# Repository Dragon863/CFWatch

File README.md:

# ⌚ CFWatch

## What is this?

CFWatch is a project that I've been wanting to build for years now. I've always dreamed of building a watch, but was never quite sure where to start - sure, the pinetime and other hackable watches were really cool, but they never quite felt "personal" or quite reflective of the stuff I enjoy. Eventually I decided I'd just build my own, but I didn't really have the knowledge or skills to do so until very recently, so when [highway](https://highway.hackclub.com/) came along I decided it was finally time! The "CF" in "CFWatch" came from [r/cassettefuturism](https://old.reddit.com/r/cassettefuturism/top/?sort=top&t=all), a huge source of design inspiration for this

## Hardware Overview (Bill of Material)

| Description | Count |
| -------- | ------- |
| USB-C charging & programming (requires bootloader) | 1 |
| red 7-segment displays | 4 |
| individually programmable buttons | 2 |
| LIR2032 battery with theoretical battery life of several months (untested) | 1 |
| SAMD21 microcontroller for low power usage | 1 |

The board layout is optimised for being assembled with JLCPCB's PCBA service, with every component apart from the battery on the front of the PCB. I would recommend hand soldering the cell mount to save costs.

## Repository Layout

The repo is structured as follows:
- PCB-related KiCad files in the `PCB/`
- FreeCAD case design in `CAD/`
- Files for creating the cover render in `Blender/`
- For a rough BOM, see `BOM.csv`
- For my development log, see `JOURNAL.md

> [!CAUTION]
> Version 1 has SEVERAL known issues! If you plan to use this to have your own manufactured, please use the V2 design made in EasyEDA and double check everything in the schematic and PCB; I am not responsible for any non-functional boards!

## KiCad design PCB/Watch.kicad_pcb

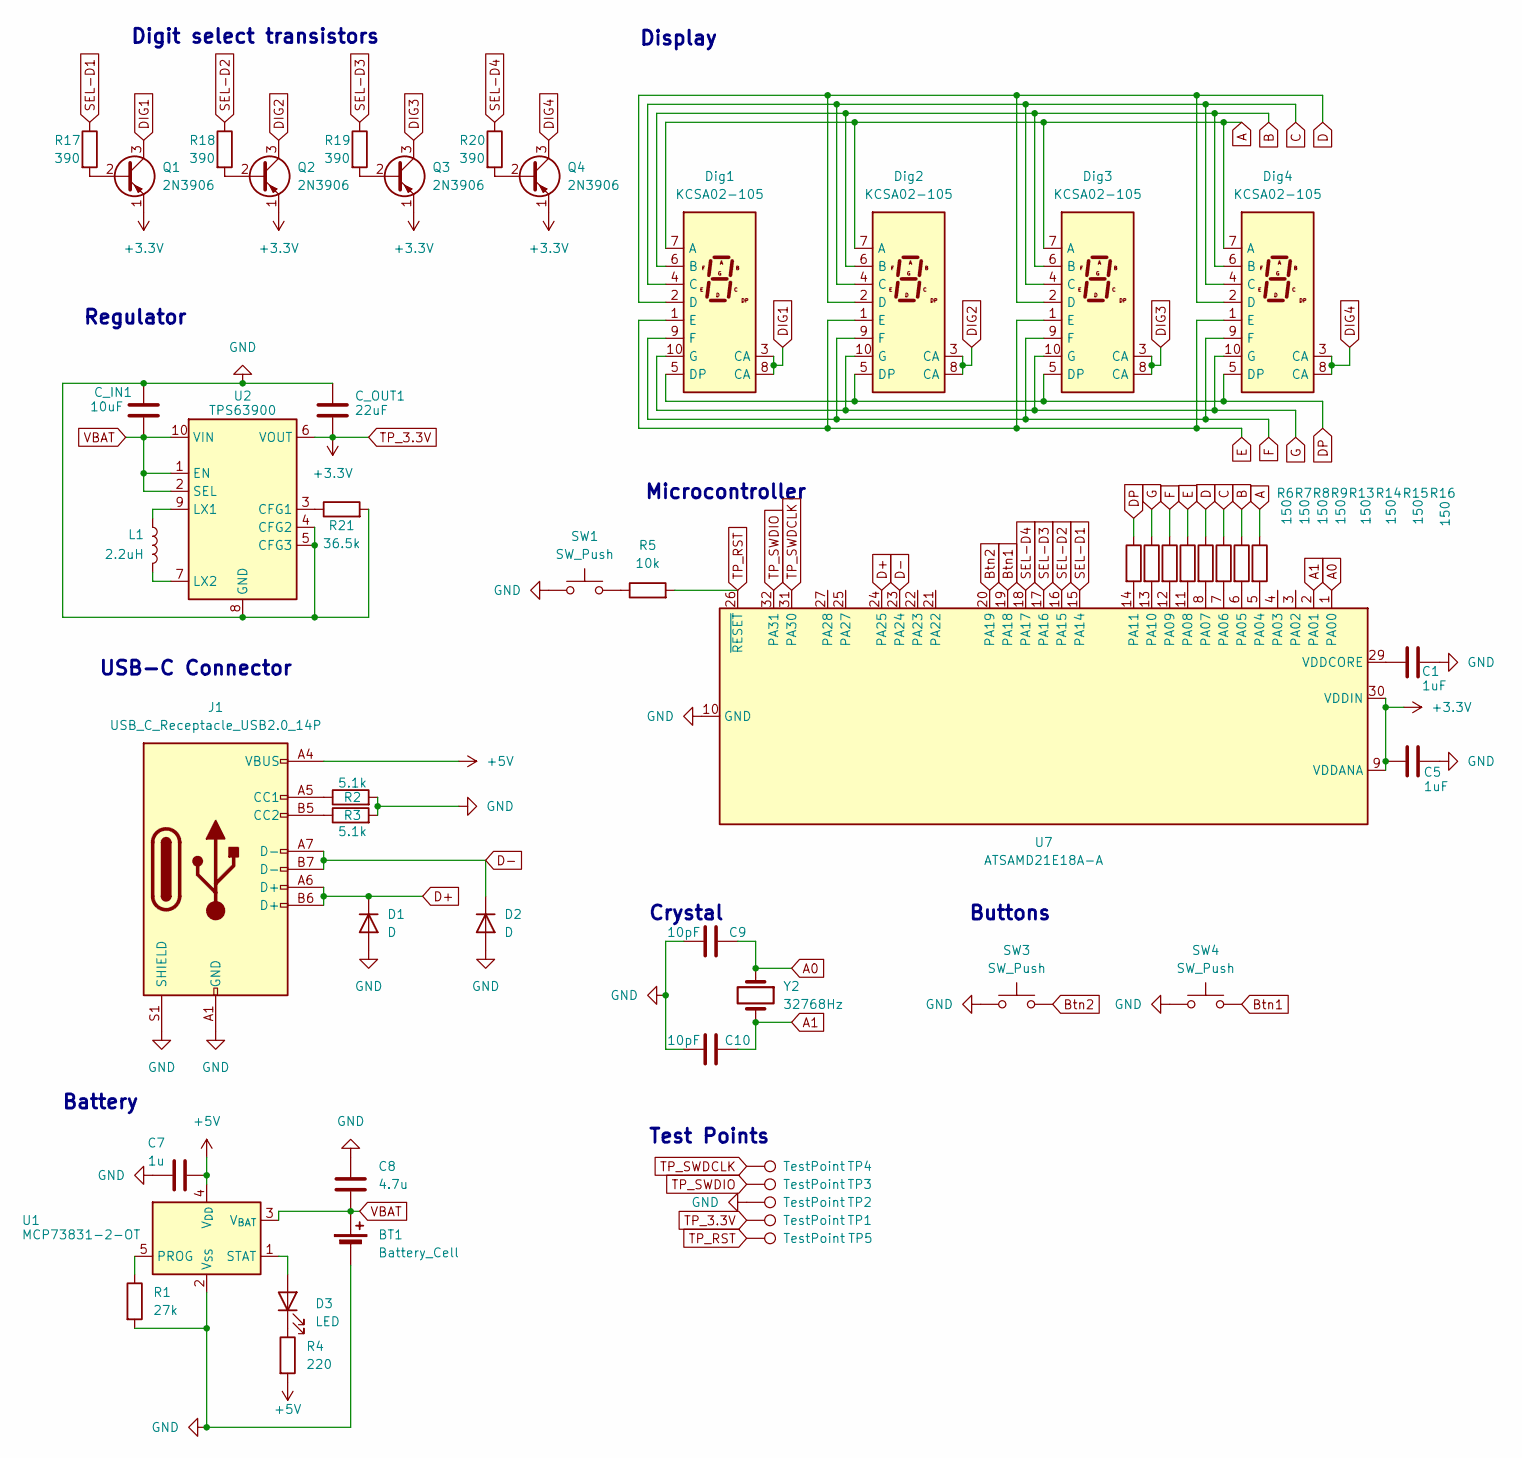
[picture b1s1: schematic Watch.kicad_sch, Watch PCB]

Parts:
BT1: Battery_Cell; BatteryHolder_Keystone_1060_1x2032
C1, C5: 1uF; C_0402_1005Metric
C7: 1u; C_0402_1005Metric
C8: 4.7u; C_0603_1608Metric
C9, C10: 10pF; C_0402_1005Metric; MPN CL21C100JBANNNC
C_IN1: 10uF; C_0603_1608Metric
C_OUT1: 22uF; C_0603_1608Metric
D1, D2: D; D_SOD-323
D3: LED; LED_0402_1005Metric
Dig1, Dig2, Dig3, Dig4: KCSA02-105; KCSC02-105
J1: USB_C_Receptacle_USB2.0_14P; USB_C_Receptacle_HCTL_HC-TYPE-C-16P-01A
L1: 2.2uH; L_0805_2012Metric
Q1, Q2, Q3, Q4: 2N3906; SOT-23
R1: 27k; R_0402_1005Metric
R2, R3: 5.1k; R_0402_1005Metric
R4: 220; R_0402_1005Metric
R5: 10k; R_0402_1005Metric
R6, R7, R8, R9, R13, R14, R15, R16: 150; R_0402_1005Metric
R17, R18, R19, R20: 390; R_0402_1005Metric
R21: 36.5k; R_0402_1005Metric
SW1, SW3, SW4: SW_Push; SW_SPST_B3U-1000P
TP1, TP2, TP3, TP4, TP5: TestPoint; TestPoint_Pad_D1.0mm
U1: MCP73831-2-OT; SOT-23-5
U2: TPS63900; WSON-10-1EP_2.5x2.5mm_P0.5mm_EP1.2x2mm_ThermalVias
U7: ATSAMD21E18A-A; TQFP-32_7x7mm_P0.8mm
Y2: 32768Hz; Crystal_SMD_3215-2Pin_3.2x1.5mm

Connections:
+5V: C7.2, J1.A4 (VBUS), J1.A9 (VBUS), J1.B4 (VBUS), J1.B9 (VBUS), R4.2, U1.4 (V_{DD})
A: Dig1.7 (A), Dig2.7 (A), Dig3.7 (A), Dig4.7 (A), R16.1
A0: C9.1, U7.1 (PA00), Y2.1
A1: C10.1, U7.2 (PA01), Y2.2
B: Dig1.6 (B), Dig2.6 (B), Dig3.6 (B), Dig4.6 (B), R15.1
Btn1: SW4.2, U7.19 (PA18)
Btn2: SW3.2, U7.20 (PA19)
C: Dig1.4 (C), Dig2.4 (C), Dig3.4 (C), Dig4.4 (C), R14.1
D: Dig1.2 (D), Dig2.2 (D), Dig3.2 (D), Dig4.2 (D), R13.1
D+: D1.1 (K), J1.A6 (D+), J1.B6 (D+), U7.24 (PA25)
D-: D2.1 (K), J1.A7 (D-), J1.B7 (D-), U7.23 (PA24)
DIG1: Dig1.3 (CA), Dig1.8 (CA), Q1.3 (C)
DIG2: Dig2.3 (CA), Dig2.8 (CA), Q2.3 (C)
DIG3: Dig3.3 (CA), Dig3.8 (CA), Q3.3 (C)
DIG4: Dig4.3 (CA), Dig4.8 (CA), Q4.3 (C)
DP: Dig1.5 (DP), Dig2.5 (DP), Dig3.5 (DP), Dig4.5 (DP), R6.1
E: Dig1.1 (E), Dig2.1 (E), Dig3.1 (E), Dig4.1 (E), R9.1
F: Dig1.9 (F), Dig2.9 (F), Dig3.9 (F), Dig4.9 (F), R8.1
G: Dig1.10 (G), Dig2.10 (G), Dig3.10 (G), Dig4.10 (G), R7.1
unnamed: D3.2 (A), U1.1 (STAT)
unnamed: D3.1 (K), R4.1
unnamed: J1.A5 (CC1), R2.1
unnamed: J1.B5 (CC2), R3.1
unnamed: Q1.2 (B), R17.2
unnamed: Q2.2 (B), R18.2
unnamed: Q3.2 (B), R19.2
unnamed: Q4.2 (B), R20.2
unnamed: R5.1, SW1.2
unnamed: R1.1, U1.5 (PROG)
unnamed: R21.1, U2.3 (CFG1)
unnamed: L1.1, U2.9 (LX1)
unnamed: L1.2, U2.7 (LX2)
unnamed: R16.2, U7.5 (PA04)
unnamed: R15.2, U7.6 (PA05)
unnamed: R14.2, U7.7 (PA06)
unnamed: R13.2, U7.8 (PA07)
unnamed: R9.2, U7.11 (PA08)
unnamed: R8.2, U7.12 (PA09)
unnamed: R7.2, U7.13 (PA10)
unnamed: R6.2, U7.14 (PA11)
unnamed: C1.1, U7.29 (VDDCORE)
SEL-D1: R17.1, U7.15 (PA14)
SEL-D2: R18.1, U7.16 (PA15)
SEL-D3: R19.1, U7.17 (PA16)
SEL-D4: R20.1, U7.18 (PA17)
TP_3.3V: C5.1, C_OUT1.2, Q1.1 (E), Q2.1 (E), Q3.1 (E), Q4.1 (E), TP1.1, U2.6 (VOUT), U7.9 (VDDANA), U7.30 (VDDIN)
TP_RST: R5.2, TP5.1, U7.26 (~RESET)
TP_SWDCLK: TP4.1, U7.31 (PA30)
TP_SWDIO: TP3.1, U7.32 (PA31)

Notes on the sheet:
Battery
Crystal
Display
Test Points
Microcontroller
Digit select transistors
Regulator
Buttons
USB-C Connector

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
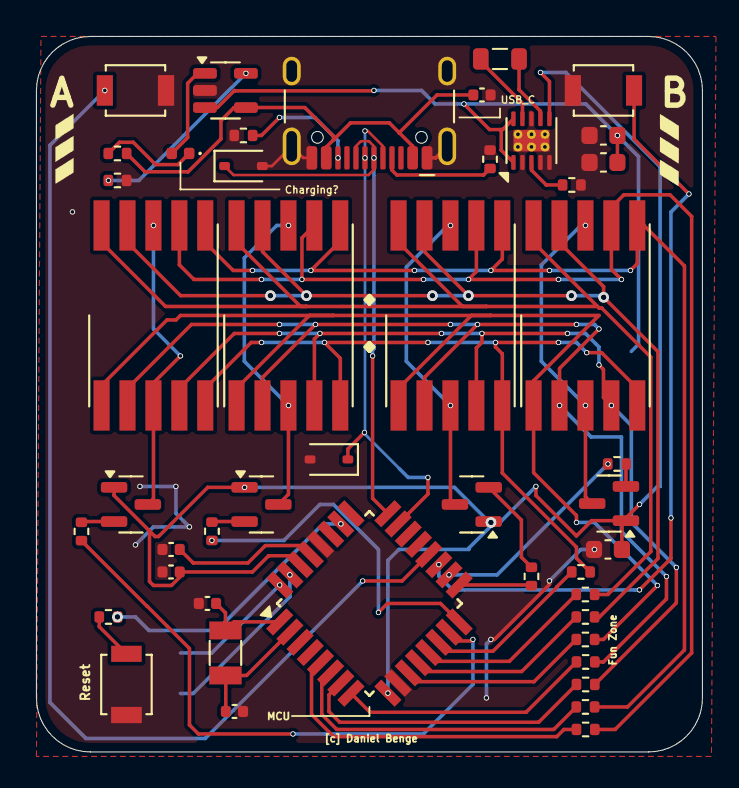
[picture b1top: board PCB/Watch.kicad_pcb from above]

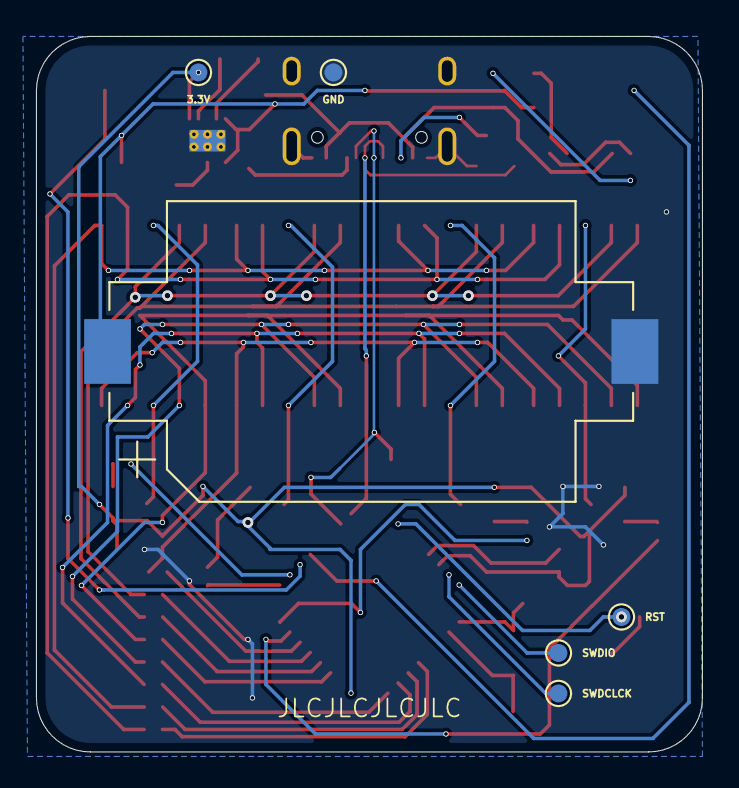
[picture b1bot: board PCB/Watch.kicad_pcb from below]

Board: 2 copper layers, 37.0 x 39.8 mm, 54 parts (6 on the bottom side), 51 nets.

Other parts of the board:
G1: LOGO
graphic2: LOGO

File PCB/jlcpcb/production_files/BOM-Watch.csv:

Comment,Designator,Footprint,LCSC,Quantity
2.2uH,L1,L_0805_2012Metric,C1043,1
MCP73831-2-OT,U1,SOT-23-5,C14879,1
36.5k,R21,R_0402_1005Metric,C15011,1
TPS63900,U2,WSON-10-1EP_2.5x2.5mm_P0.5mm_EP1.2x2mm_ThermalVias,C1518762,1
D,"D1,D2",D_SOD-323,C191023,2
4.7u,C8,C_0603_1608Metric,C19666,1
KCSA02-105,"Dig1,Dig2,Dig3,Dig4",KCSC02-105,C22462656,4
SW_Push,"SW1,SW3,SW4",SW_SPST_B3U-1000P,C231329,3
150,"R13,R14,R15,R16,R6,R7,R8,R9",R_0402_1005Metric,C25082,8
220,R4,R_0402_1005Metric,C25091,1
390,"R17,R18,R19,R20",R_0402_1005Metric,C25109,4
10k,R5,R_0402_1005Metric,C25744,1
27k,R1,R_0402_1005Metric,C25771,1
5.1k,"R2,R3",R_0402_1005Metric,C25905,2
USB_C_Receptacle_USB2.0_14P,J1,USB_C_Receptacle_HCTL_HC-TYPE-C-16P-01A,C2988369,1
32768Hz,Y2,Crystal_SMD_3215-2Pin_3.2x1.5mm,C32346,1
10pF,"C10,C9",C_0402_1005Metric,C32949,2
LED,D3,LED_0402_1005Metric,C33115,1
1uF,"C1,C5,C6,C7",C_0402_1005Metric,C52923,4
2N3906,"Q1,Q2,Q3,Q4",SOT-23,C5300004,4
22uF,C_OUT1,C_0603_1608Metric,C59461,1
ATSAMD21E18A-A,U7,TQFP-32_7x7mm_P0.8mm,C618770,1
10uF,C_IN1,C_0603_1608Metric,C96446,1

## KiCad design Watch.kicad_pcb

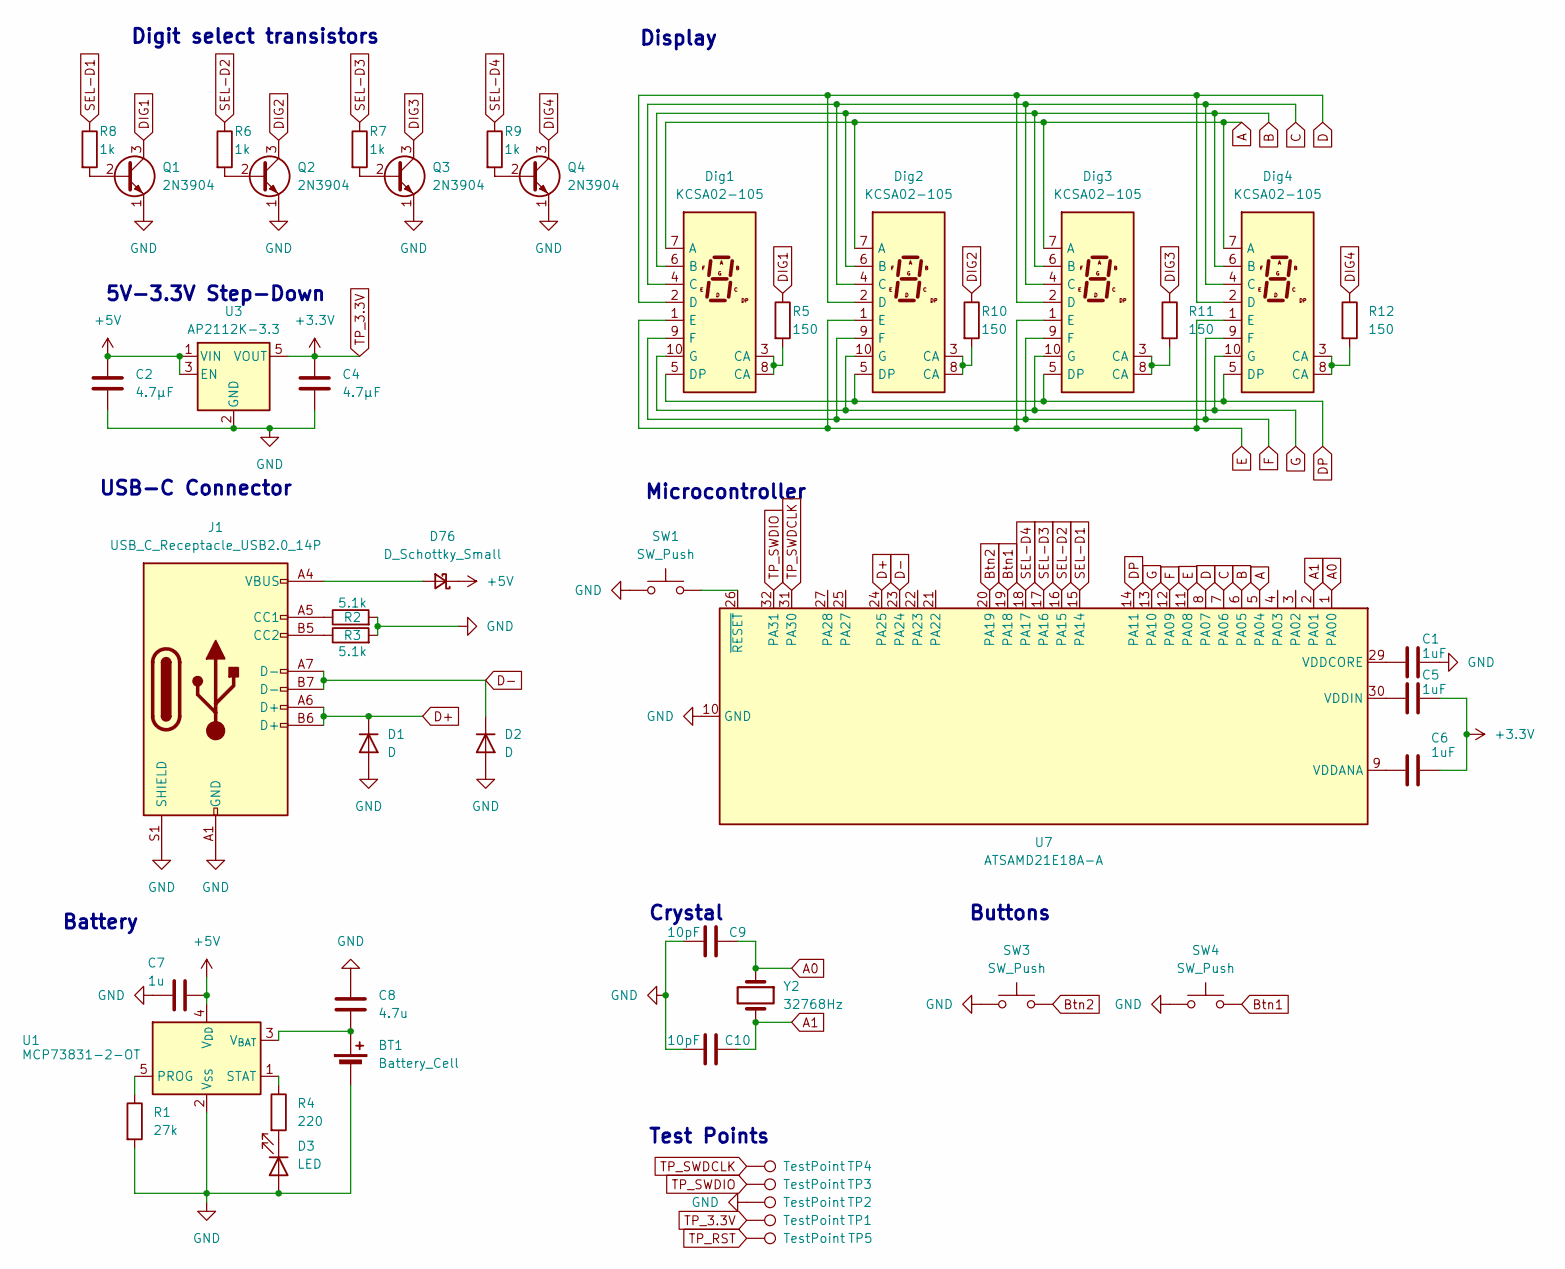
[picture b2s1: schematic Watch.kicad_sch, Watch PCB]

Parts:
BT1: Battery_Cell; BatteryHolder_Keystone_1060_1x2032
C1, C5, C6: 1uF; C_0603_1608Metric
C2, C4: 4.7µF; C_0603_1608Metric
C7: 1u; C_0603_1608Metric
C8: 4.7u; C_0603_1608Metric
C9, C10: 10pF; C_0603_1608Metric; MPN CL21C100JBANNNC
D1, D2: D; D_SOD-323
D3: LED; LED_0603_1608Metric
D76: D_Schottky_Small; D_SOD-323
Dig1, Dig2, Dig3, Dig4: KCSA02-105; KCSC02-105
J1: USB_C_Receptacle_USB2.0_14P; USB_C_Receptacle_HCTL_HC-TYPE-C-16P-01A
Q1, Q2, Q3, Q4: 2N3904; SOT-23
R1: 27k; R_0603_1608Metric
R2, R3: 5.1k; R_0603_1608Metric
R4: 220; R_0603_1608Metric
R5, R10, R11, R12: 150; R_0603_1608Metric
R6, R7, R8, R9: 1k; R_0603_1608Metric
SW1, SW3, SW4: SW_Push; SW_SPST_B3U-1000P
TP1, TP2, TP3, TP4: TestPoint; TestPoint_Pad_D1.0mm
TP5: TestPoint
U1: MCP73831-2-OT; SOT-23-5
U3: AP2112K-3.3; SOT-23-5
U7: ATSAMD21E18A-A; TQFP-32_7x7mm_P0.8mm
Y2: 32768Hz; Crystal_SMD_3215-2Pin_3.2x1.5mm

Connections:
+5V: C2.1, C7.2, D76.1 (K), U1.4 (V_{DD}), U3.1 (VIN), U3.3 (EN)
A: Dig1.7 (A), Dig2.7 (A), Dig3.7 (A), Dig4.7 (A), U7.5 (PA04)
A0: C9.1, U7.1 (PA00), Y2.1
A1: C10.1, U7.2 (PA01), Y2.2
B: Dig1.6 (B), Dig2.6 (B), Dig3.6 (B), Dig4.6 (B), U7.6 (PA05)
Btn1: SW4.2, U7.19 (PA18)
Btn2: SW3.2, U7.20 (PA19)
C: Dig1.4 (C), Dig2.4 (C), Dig3.4 (C), Dig4.4 (C), U7.7 (PA06)
D: Dig1.2 (D), Dig2.2 (D), Dig3.2 (D), Dig4.2 (D), U7.8 (PA07)
D+: D1.1 (K), J1.A6 (D+), J1.B6 (D+), U7.24 (PA25)
D-: D2.1 (K), J1.A7 (D-), J1.B7 (D-), U7.23 (PA24)
DIG1: Q1.3 (C), R5.1
DIG2: Q2.3 (C), R10.1
DIG3: Q3.3 (C), R11.1
DIG4: Q4.3 (C), R12.1
DP: Dig1.5 (DP), Dig2.5 (DP), Dig3.5 (DP), Dig4.5 (DP), U7.14 (PA11)
E: Dig1.1 (E), Dig2.1 (E), Dig3.1 (E), Dig4.1 (E), U7.11 (PA08)
F: Dig1.9 (F), Dig2.9 (F), Dig3.9 (F), Dig4.9 (F), U7.12 (PA09)
G: Dig1.10 (G), Dig2.10 (G), Dig3.10 (G), Dig4.10 (G), U7.13 (PA10)
GND: BT1.2 (-), C1.2, C2.2, C4.2, C7.1, C8.1, C9.2, C10.2, D1.2 (A), D2.2 (A), D3.2 (A), J1.A1 (GND), J1.A12 (GND), J1.B1 (GND), J1.B12 (GND), J1.S1 (SHIELD), Q1.1 (E), Q2.1 (E), Q3.1 (E), Q4.1 (E), R1.2, R2.2, R3.2, SW1.1, SW3.1, SW4.1, TP2.1, U1.2 (V_{SS}), U3.2 (GND), U7.10 (GND), U7.28 (GND)
unnamed: BT1.1 (+), C8.2, U1.3 (V_{BAT})
unnamed: D3.1 (K), R4.2
unnamed: D76.2 (A), J1.A4 (VBUS), J1.A9 (VBUS), J1.B4 (VBUS), J1.B9 (VBUS)
unnamed: Dig1.3 (CA), Dig1.8 (CA), R5.2
unnamed: Dig2.3 (CA), Dig2.8 (CA), R10.2
unnamed: Dig3.3 (CA), Dig3.8 (CA), R11.2
unnamed: Dig4.3 (CA), Dig4.8 (CA), R12.2
unnamed: J1.A5 (CC1), R2.1
unnamed: J1.B5 (CC2), R3.1
unnamed: Q1.2 (B), R8.2
unnamed: Q2.2 (B), R6.2
unnamed: Q3.2 (B), R7.2
unnamed: Q4.2 (B), R9.2
unnamed: R1.1, U1.5 (PROG)
unnamed: R4.1, U1.1 (STAT)
unnamed: C6.1, U7.9 (VDDANA)
unnamed: C1.1, U7.29 (VDDCORE)
unnamed: C5.1, U7.30 (VDDIN)
unnamed: SW1.2, U7.26 (~RESET)
SEL-D1: R8.1, U7.15 (PA14)
SEL-D2: R6.1, U7.16 (PA15)
SEL-D3: R7.1, U7.17 (PA16)
SEL-D4: R9.1, U7.18 (PA17)
TP_3.3V: C4.1, C5.2, C6.2, TP1.1, U3.5 (VOUT)
TP_SWDCLK: TP4.1, U7.31 (PA30)
TP_SWDIO: TP3.1, U7.32 (PA31)

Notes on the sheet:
Battery
Crystal
Display
Test Points
Microcontroller
Digit select transistors
5V-3.3V Step-Down
Buttons
USB-C Connector

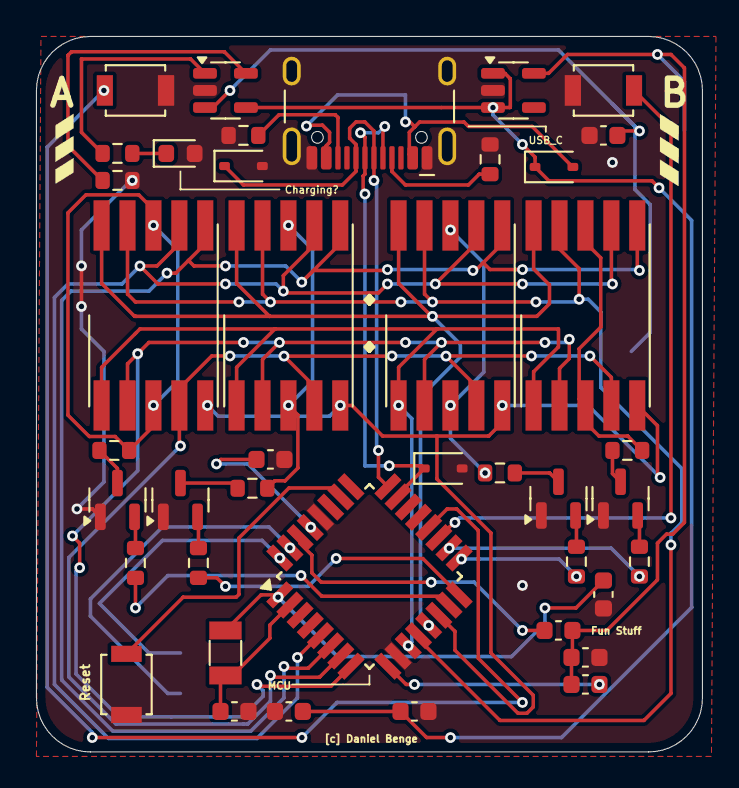
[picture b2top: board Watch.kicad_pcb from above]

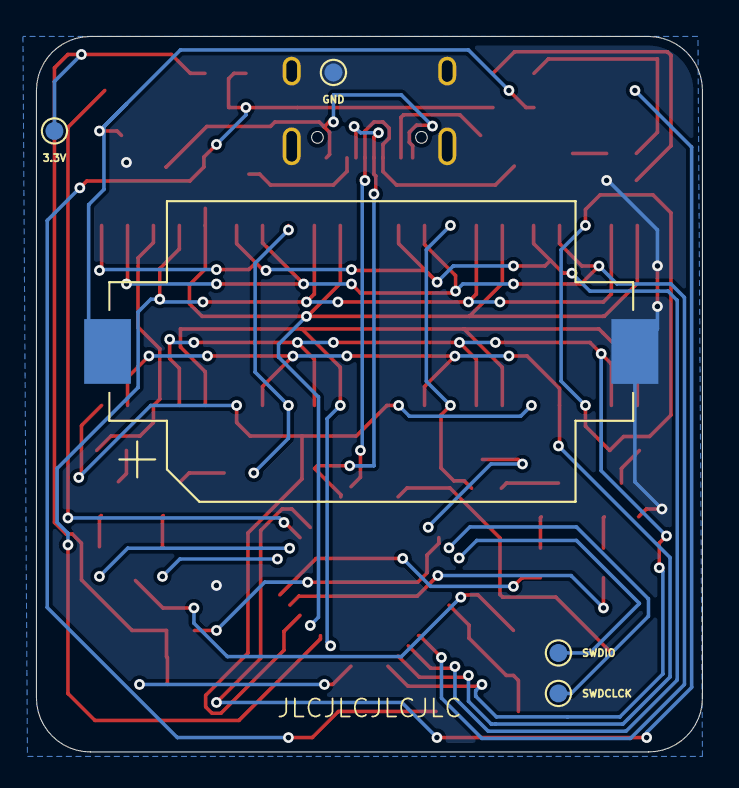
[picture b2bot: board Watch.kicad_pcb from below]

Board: 2 copper layers, 37.0 x 39.8 mm, 48 parts (5 on the bottom side), 46 nets.

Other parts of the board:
G1: LOGO
graphic2: LOGO

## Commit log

2025-05-17 Ignore jlcpcb
2025-05-19 session 2
2025-05-20 Fix typos, formatting
2025-05-23 Add session 3
2025-05-23 Add header
2025-05-23 Fix date
2025-05-27 Add blender, session 4, new render
2025-05-28 Fix PCB by adding test points
2025-05-28 Better test points
2025-05-28 Tiny improvements
2025-05-28 Session 5 + BOM
2025-05-28 Add csv BOM
2025-05-28 Add time spent
2025-05-28 Restructure everything :)
2025-06-11 Switch regulator
2025-06-11 Fix charge LED, display resistors
2025-06-11 Add resistor to reset button, small schematic changes
2025-06-14 Reformatted bill of material (BOM) to table
    Reformatted bill-of-material to table in the README so it resembles more what a BOM usually looks like.
2025-07-01 Update render, PCB
2025-07-07 Fix regulator and voltage issue, replace inductor with LED
2025-07-16 Update for V2
